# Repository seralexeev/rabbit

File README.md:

# Rabbit

A small home-built Ackermann rover that maps a flat on its own, drives to things you name ("drive to the fridge") and explains what it did. Everything is in this repo: the robot code, the web HUD, the telemetry store with its AI agent, the hardware design for the next version, and the build log.

Build log (Russian and English): **[rabbit0.dev](https://rabbit0.dev)** · Live HUD: https://live.rabbit0.dev (by personal link)

## What it does

- **Maps and localizes with one stereo camera.** A ZED 2i provides depth, visual-inertial odometry and object detection. nvblox builds a voxel map and a clearance grid on the GPU, and the robot relocalizes in its saved map after a restart. Relocalizing after being carried to another room is the open problem; RTAB-Map is replacing ZED GEN_3 for it.
- **Plans and drives like a car.** A Hybrid A* planner knows the robot's asymmetric turning radius and plans forward and reverse manoeuvres. A path tracker follows the plan on the rear axle, and a collision guard checks the swept footprint against the live obstacle scan.
- **Explores by itself.** It picks views by information gain and finishes a room before leaving it.
- **Takes orders in plain language.** The HUD chat, by text or voice, talks to Forge, an agent that answers from the recorded telemetry ("why did it stop at 03:12?") and can send trips after the operator approves them.
- **Records everything.** Every pose, command, decision with its reason, log line and power sample goes into Parquet files, queried with chDB (embedded ClickHouse).
- **Runs headless.** The HUD is only a viewer: the robot doesn't care whether anyone is watching.

| | |
|---|---|
|  |  |

## Hardware

| Part | What |
|---|---|
| Chassis | "Red Ackerman Racing Car" metal kit; front steering, rear drive. Wheelbase 0.17 m, 75 mm wheels, ~3.5 kg |
| Brain | NVIDIA Jetson Orin Nano Super 8 GB (JetPack 6, MAXN_SUPER, headless) |
| Camera | Stereolabs ZED 2i (depth, VIO, IMU, barometer, magnetometer) |
| Drive | 2 × Pololu 37D 70:1 12 V gearmotors on a RoboClaw 2x30A; electronic differential in software |
| Steering | AGFRC A50BHL brushless servo via a PCA9685 |
| Power | NEEWER PS099E V-mount battery (99 Wh, 4S Li-ion) and Pololu step-down regulators; INA4235 4-channel power monitor |
| Network | Wi-Fi only; NATS over websockets for the HUD; a Cloudflare tunnel for public access |

## Software

Python nodes talk over [NATS](https://nats.io) instead of ROS, one Docker container per node on the Jetson.

```
 ZED 2i ─► rabbit-zed ──pose/odom, obstacle scan, objects, map──► rabbit-nav ──drive──► rabbit-roboclaw ─► motors
              │                                              ▲        │                rabbit-steering ─► servo
              └─► rabbit-loc (RTAB-Map, map←odom)            │        └─ safety trips, recovery
                                   rabbit-planner (Hybrid A*) ┤
                                   rabbit-explore (frontiers) ┘
 rabbit-ina, rabbit-telemetry ─► power, Jetson, Docker, Wi-Fi
 all subjects ─► Forge (Parquet + chDB) ─► slabs, MCP, HUD chat agent
 HUD (React, three.js, uPlot) ◄── NATS websocket, served by rabbit-web (nginx)
```

| Path | What |
|---|---|
| [`workspaces/rabbit`](workspaces/rabbit) | robot nodes (`src/node/`), libraries (`src/lib/`), native extensions (nvblox, RTAB-Map), tests, the simulator |
| [`workspaces/web`](workspaces/web) | the HUD |
| [`workspaces/forge`](workspaces/forge) | Forge: telemetry writer, store, slabs, metric graph, MCP server and chat agent ([README](workspaces/forge/README.md)) |
| [`workspaces/blog`](workspaces/blog) | the build log at rabbit0.dev |
| [`workspaces/bench`](workspaces/bench) | localization benchmark and recording tools |
| [`workspaces/compose.yaml`](workspaces/compose.yaml), [`workspaces/nats`](workspaces/nats), [`workspaces/jetson`](workspaces/jetson) | services, NATS config, Jetson boot tuning |
| [`pcb/rabbit-body`](pcb/rabbit-body), [`cad/brackets`](cad/brackets), [`model`](model) | Rabbit 2.0 body PCB, 3D-printed mounts, chassis model |
| [`docs`](docs) | engineering log, reports, roadmap, open issues, lessons |
| [`scripts`](scripts) | deploy, bring-up, simulator, access links, blog |

## Rabbit 2.0

The next version splits the robot into a **brain** and a **body**:
- the Jetson keeps only GPU work: perception, localization and planning;
- a Raspberry Pi 4 becomes the body. It runs the motors, the steering, the power, an independent safety loop, a 360° lidar, ToF sensors and bumpers, a rear camera, Forge and the HUD.

The body electronics move from an acrylic deck full of modules onto one PCB shaped like the chassis deck. The board is generated from Python with KiCad and Freerouting.

| | |
|---|---|
|  |  |
|  |  |

Design: [architecture](docs/reports/2026-10-03-architecture-2.0.md) · [wiring](docs/reports/2026-10-03-architecture-2.0-wiring.md) · [BOM](docs/reports/2026-10-03-architecture-2.0-bom.md) · [body PCB](docs/reports/2026-10-03-body-pcb.md) · [mounts](docs/reports/2026-10-03-mounts.md) · [power](docs/reports/media/power-2.0.svg)

## Working on it

The project is developed mostly by coding agents. [`AGENTS.md`](AGENTS.md) holds the rules, and the skills in [`.claude/skills`](.claude/skills) hold the procedures:
- `rabbit-robot`: operating and deploying the robot;
- `rabbit-dev`: robot code and the HUD;
- `forge-dev`: Forge;
- `rabbit-blog`: the blog.

```sh
# robot tests
cd workspaces/rabbit && uv run --no-project --python 3.10 --with pytest --with numpy --with pydantic --with numba --with nats-py python -m pytest tests -q

# full-stack simulator on the Mac: local NATS + rabbit-sim + the real nav, planner and explore
scripts/sim.sh

# HUD dev server at https://localhost:3005
cd workspaces/web && node ../../.yarn/releases/yarn-4.9.3.cjs dev

# deploy named services to the robot
scripts/deploy.sh rabbit-nav rabbit-web

# after the robot was off: checks, deploy, tests, step by step
uv run scripts/bringup.py check
```

## Work log and blog

Every piece of significant work leaves two traces, written as part of the work:

1. **Engineering log** in [`docs/`](docs/README.md), in English and factual:
   - `docs/log/YYYY-MM-DD-<topic>.md`: what was tried and dropped, numbers, root causes;
   - [`docs/roadmap.md`](docs/roadmap.md): what's next;
   - [`docs/open-issues.md`](docs/open-issues.md): open questions and unresolved problems;
   - [`docs/lessons.md`](docs/lessons.md): rules learned the hard way.
2. **Blog post** at [rabbit0.dev](https://rabbit0.dev), in the author's voice:
   - source in [`workspaces/blog`](workspaces/blog): `README.ru.md` holds the Russian posts, `README.md` the English ones, `static/media/` the media;
   - `scripts/blog.sh build` renders the pages;
   - a push to `main` that touches `workspaces/blog` deploys it to GitHub Pages ([`.github/workflows/blog.yml`](.github/workflows/blog.yml)).

## Access links

The public HUD at https://live.rabbit0.dev opens only through a personal link; the LAN address (https://jetson.rabbit) stays open. Ask the agent "give me a link" (optionally "for Alice") or "remove Alice's link", or run it yourself:

```sh
scripts/links.sh              # list: name, date, link
scripts/links.sh add alice    # create a link, prints https://live.rabbit0.dev/k/<token>
scripts/links.sh rm alice     # revoke it: the open HUD is cut off within ~5 s
```

The registry lives only on the robot, in `/root/rabbit/workspaces/links/links.map`. Details are in the `rabbit-robot` skill.

Old hardware and setup scratch notes: [`docs/notes.md`](docs/notes.md).

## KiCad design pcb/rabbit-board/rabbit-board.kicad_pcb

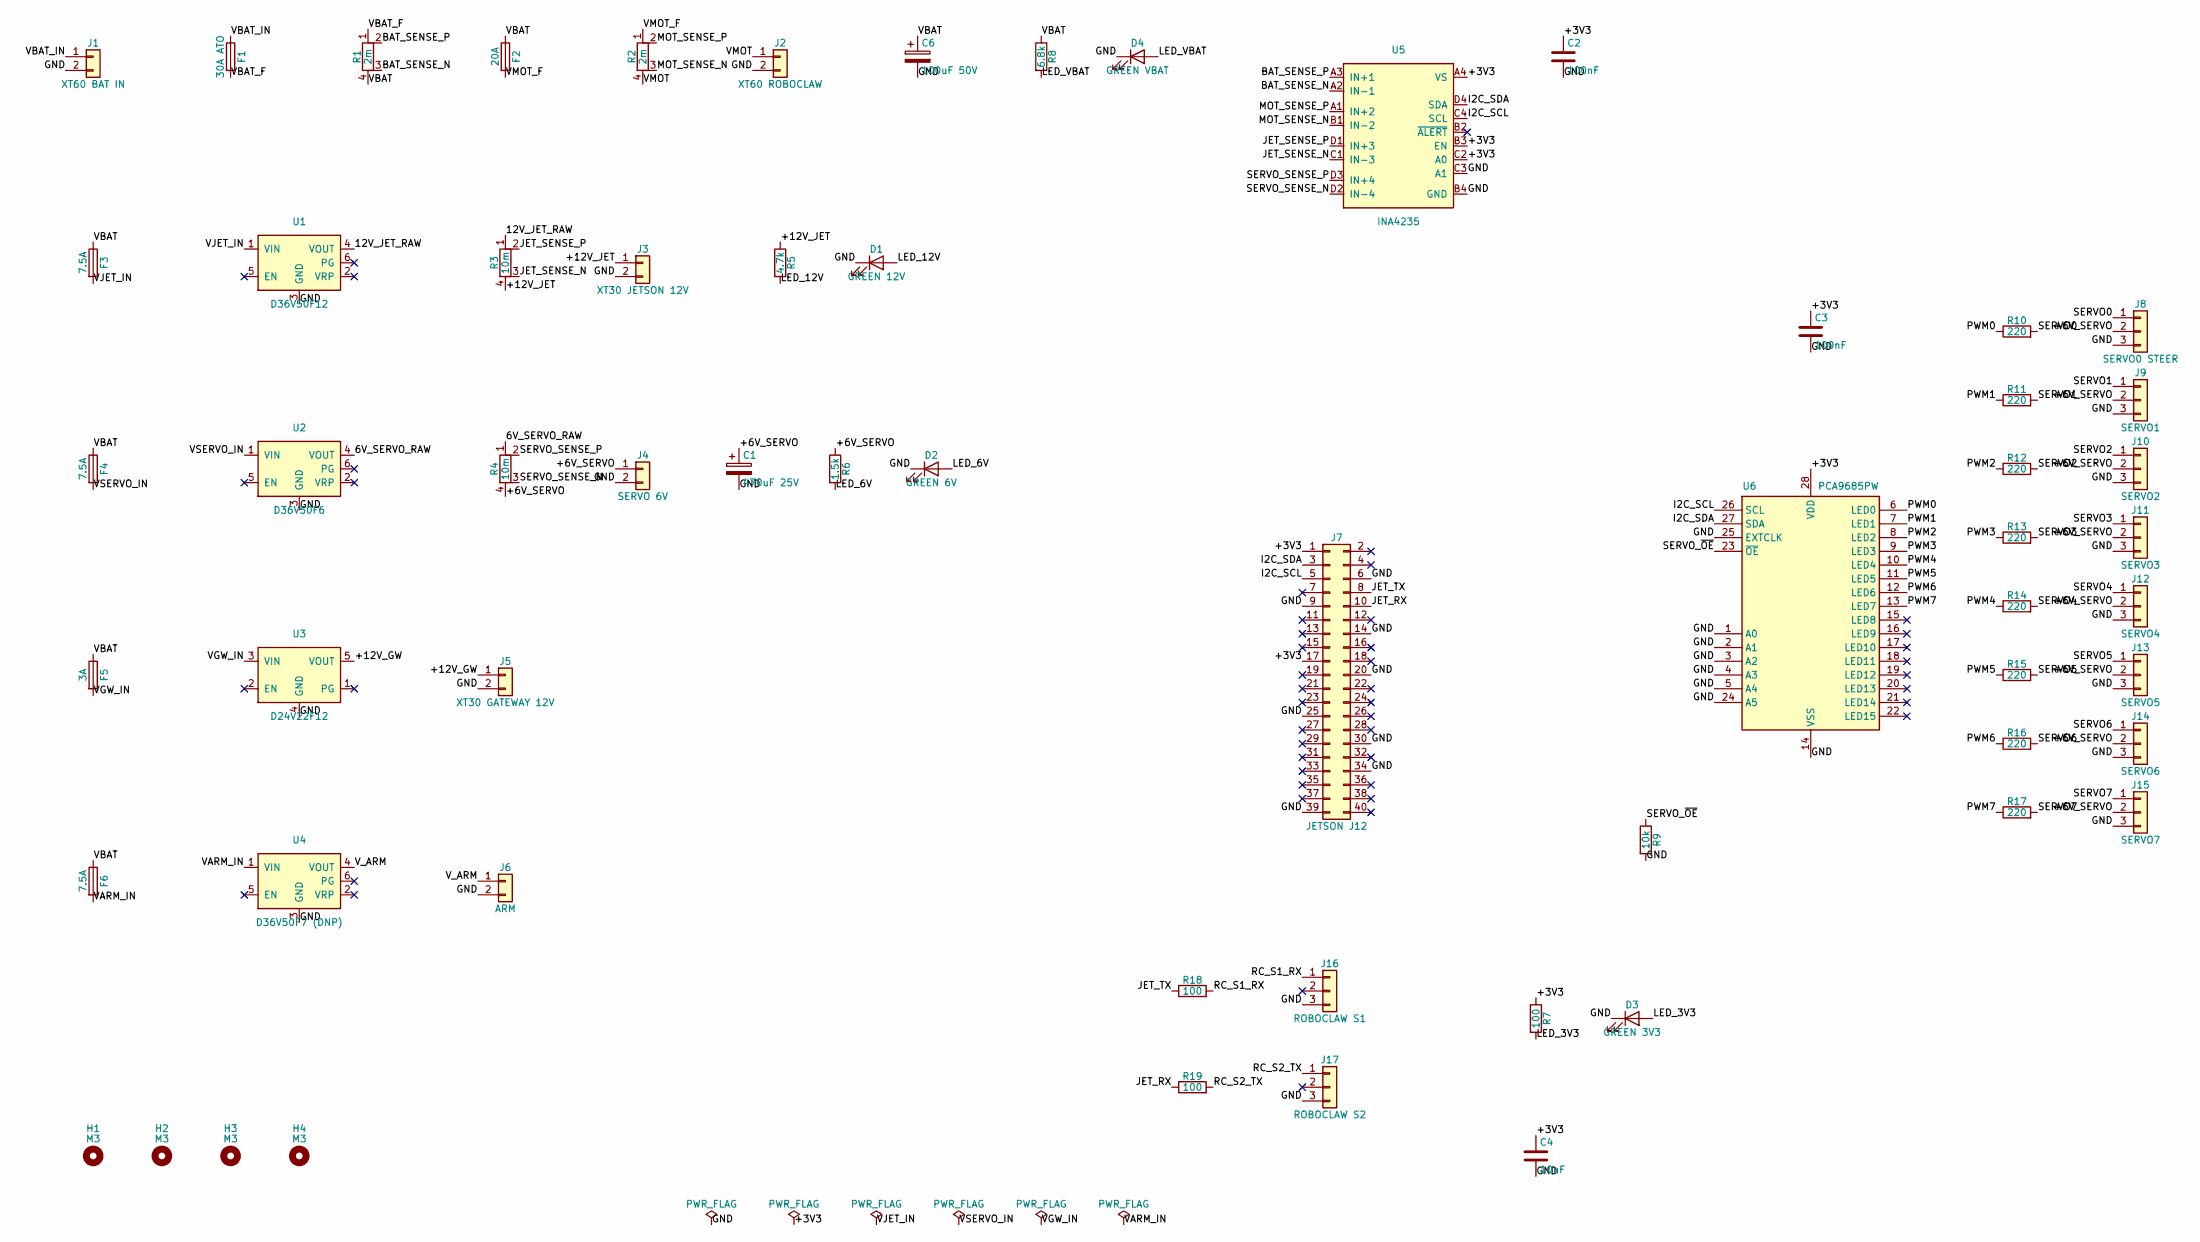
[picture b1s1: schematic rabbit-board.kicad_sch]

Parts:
C1: 470uF 25V; CP_Elec_8x10.5; LCSC C48935394
C2, C3: 100nF; C_0603_1608Metric; LCSC C14663
C4: 10uF; C_0805_2012Metric; LCSC C15850
C6: 100uF 50V; CP_Elec_6.3x7.7; LCSC C46550415
D1: GREEN 12V; LED_0805_2012Metric; LCSC C2297
D2: GREEN 6V; LED_0805_2012Metric; LCSC C2297
D3: GREEN 3V3; LED_0805_2012Metric; LCSC C2297
D4: GREEN VBAT; LED_0805_2012Metric; LCSC C2297
F1: 30A ATO; FuseHolder_Blade_ATO_Littelfuse_FLR_178.6165
F2: 20A; Fuseholder_Blade_Mini_Keystone_3568
F3, F4, F6: 7.5A; Fuseholder_Blade_Mini_Keystone_3568
F5: 3A; Fuseholder_Blade_Mini_Keystone_3568
H1, H2, H3, H4: M3; MountingHole_3.2mm_M3
J1: XT60 BAT IN; AMASS_XT60PW-M_1x02_P7.20mm_Horizontal
J2: XT60 ROBOCLAW; AMASS_XT60PW-F_1x02_P7.20mm_Horizontal
J3: XT30 JETSON 12V; AMASS_XT30PW-F_1x02_P2.50mm_Horizontal
J4: SERVO 6V; TerminalBlock_Phoenix_MKDS-1,5-2-5.08_1x02_P5.08mm_Horizont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
J5: XT30 GATEWAY 12V; AMASS_XT30PW-F_1x02_P2.50mm_Horizontal
J6: ARM; TerminalBlock_Phoenix_MKDS-1,5-2-5.08_1x02_P5.08mm_Horizont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
J7: JETSON J12; IDC-Header_2x20_P2.54mm_Vertical
J8: SERVO0 STEER; PinHeader_1x03_P2.54mm_Vertical
J9: SERVO1; PinHeader_1x03_P2.54mm_Vertical
J10: SERVO2; PinHeader_1x03_P2.54mm_Vertical
J11: SERVO3; PinHeader_1x03_P2.54mm_Vertical
J12: SERVO4; PinHeader_1x03_P2.54mm_Vertical
J13: SERVO5; PinHeader_1x03_P2.54mm_Vertical
J14: SERVO6; PinHeader_1x03_P2.54mm_Vertical
J15: SERVO7; PinHeader_1x03_P2.54mm_Vertical
J16: ROBOCLAW S1; PinHeader_1x03_P2.54mm_Vertical
J17: ROBOCLAW S2; PinHeader_1x03_P2.54mm_Vertical
R1, R2: 2m; R_Shunt_Vishay_WSK2512_6332Metric_T1.19mm; LCSC C3997408
R3, R4: 10m; R_Shunt_Vishay_WSK2512_6332Metric_T1.19mm; LCSC C3985410
R5: 4.7k; R_0603_1608Metric; LCSC C23162
R6: 1.5k; R_0603_1608Metric; LCSC C22843
R7, R18, R19: 100; R_0603_1608Metric; LCSC C22775
R8: 6.8k; R_0603_1608Metric; LCSC C23212
R9: 10k; R_0603_1608Metric; LCSC C25804
R10, R11, R12, R13, R14, R15, R16, R17: 220; R_0603_1608Metric; LCSC C22962
U1: D36V50F12; Pololu_D36V50Fx
U2: D36V50F6; Pololu_D36V50Fx
U3: D24V22F12; Pololu_D24V22Fx
U4: D36V50F7 (DNP); Pololu_D36V50Fx
U5: INA4235; TI_DSBGA-16_YBJ_1.5x1.5mm_P0.4mm; LCSC C33440856
U6: PCA9685PW; TSSOP-28_4.4x9.7mm_P0.65mm; LCSC C2678753

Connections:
/6V_SERVO_RAW: R4.1, U2.4 (VOUT)
/12V_JET_RAW: R3.1, U1.4 (VOUT)
/+3V3: C2.1, C3.1, C4.1, J7.1, J7.17, R7.1, U5.A4 (VS), U5.B3 (EN), U5.C2 (A0), U6.28 (VDD)
/+6V_SERVO: C1.1, J4.1, J8.2, J9.2, J10.2, J11.2, J12.2, J13.2, J14.2, J15.2, R4.4, R6.1
/+12V_GW: J5.1, U3.5 (VOUT)
/+12V_JET: J3.1, R3.4, R5.1
/BAT_SENSE_N: R1.3, U5.A2 (IN-1)
/BAT_SENSE_P: R1.2, U5.A3 (IN+1)
/GND: C1.2, C2.2, C3.2, C4.2, C6.2, D1.1 (K), D2.1 (K), D3.1 (K), D4.1 (K), J1.2, J2.2, J3.2, J4.2, J5.2, J6.2, J7.6, J7.9, J7.14, J7.20, J7.25, J7.30, J7.34, J7.39, J8.3, J9.3, J10.3, J11.3, J12.3, J13.3, J14.3, J15.3, J16.3, J17.3, R9.2, U1.3 (GND), U2.3 (GND), U3.4 (GND), U4.3 (GND), U5.B4 (GND), U5.C3 (A1), U6.1 (A0), U6.2 (A1), U6.3 (A2), U6.4 (A3), U6.5 (A4), U6.14 (VSS), U6.24 (A5), U6.25 (EXTCLK)
/I2C_SCL: J7.5, U5.C4 (SCL), U6.26 (SCL)
/I2C_SDA: J7.3, U5.D4 (SDA), U6.27 (SDA)
/JET_RX: J7.10, R19.1
/JET_SENSE_N: R3.3, U5.C1 (IN-3)
/JET_SENSE_P: R3.2, U5.D1 (IN+3)
/JET_TX: J7.8, R18.1
/LED_3V3: D3.2 (A), R7.2
/LED_6V: D2.2 (A), R6.2
/LED_12V: D1.2 (A), R5.2
/LED_VBAT: D4.2 (A), R8.2
/MOT_SENSE_N: R2.3, U5.B1 (IN-2)
/MOT_SENSE_P: R2.2, U5.A1 (IN+2)
/PWM0: R10.1, U6.6 (LED0)
/PWM1: R11.1, U6.7 (LED1)
/PWM2: R12.1, U6.8 (LED2)
/PWM3: R13.1, U6.9 (LED3)
/PWM4: R14.1, U6.10 (LED4)
/PWM5: R15.1, U6.11 (LED5)
/PWM6: R16.1, U6.12 (LED6)
/PWM7: R17.1, U6.13 (LED7)
/RC_S1_RX: J16.1, R18.2
/RC_S2_TX: J17.1, R19.2
/SERVO0: J8.1, R10.2
/SERVO1: J9.1, R11.2
/SERVO2: J10.1, R12.2
/SERVO3: J11.1, R13.2
/SERVO4: J12.1, R14.2
/SERVO5: J13.1, R15.2
/SERVO6: J14.1, R16.2
/SERVO7: J15.1, R17.2
/SERVO_SENSE_N: R4.3, U5.D2 (IN-4)
/SERVO_SENSE_P: R4.2, U5.D3 (IN+4)
/SERVO_~OE: R9.1, U6.23 (~OE)
/VARM_IN: F6.2, U4.1 (VIN)
/VBAT: C6.1, F2.1, F3.1, F4.1, F5.1, F6.1, R1.4, R8.1
/VBAT_F: F1.2, R1.1
/VBAT_IN: F1.1, J1.1
/VGW_IN: F5.2, U3.3 (VIN)
/VJET_IN: F3.2, U1.1 (VIN)
/VMOT: J2.1, R2.4
/VMOT_F: F2.2, R2.1
/VSERVO_IN: F4.2, U2.1 (VIN)
/V_ARM: J6.1, U4.4 (VOUT)

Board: 4 copper layers, 61 parts (0 on the bottom side), 52 nets, no tracks yet.

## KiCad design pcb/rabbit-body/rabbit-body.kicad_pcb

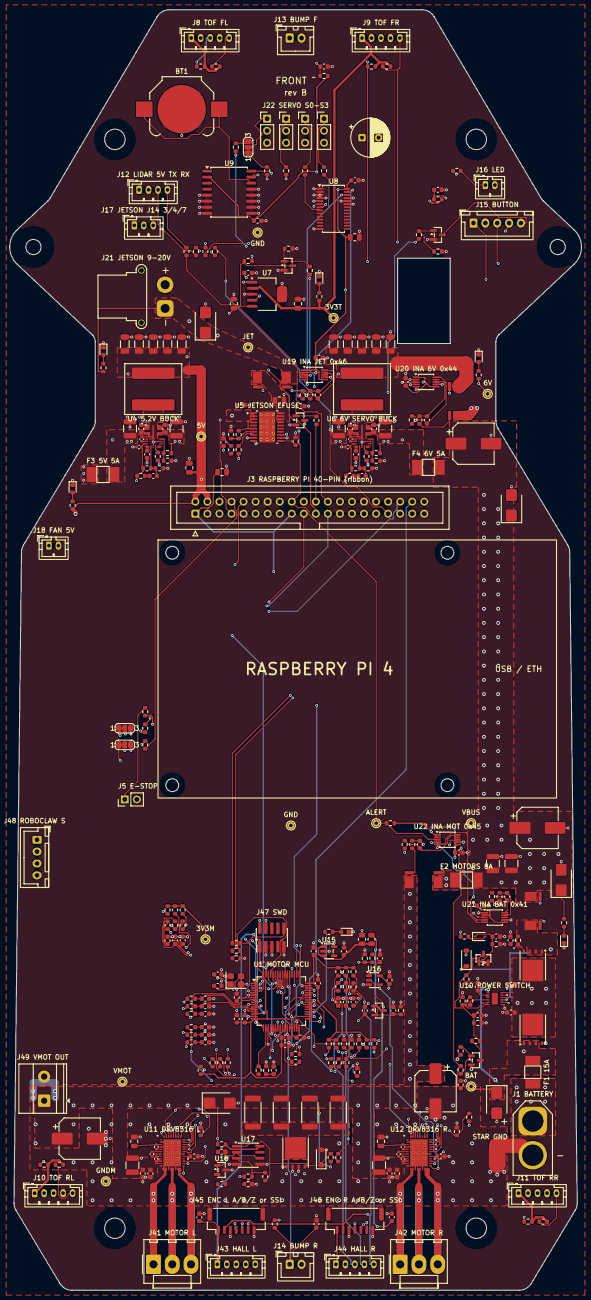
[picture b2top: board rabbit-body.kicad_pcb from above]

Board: 4 copper layers, 120.5 x 269.9 mm, 346 parts (0 on the bottom side), 226 nets.

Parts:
BT1: CR1220; BatteryHolder_Keystone_3000_1x12mm
C3, C5, C10, C11, C12, C14A, C14B, C19, C20, C21, C22, C26, C27, C28, C29, C63, C70, C71, C72, C73, C81, C83, C87, C120, C121, C122, C123, C1101, C1102, C1201, C1202: 100nF; C_0603_1608Metric
C4, C6, C7, C9, C13, C1106, C1206: 10uF; C_0805_2012Metric
C8, C24, C86: 10nF; C_0603_1608Metric
C14: 470uF 16V; CP_Radial_D8.0mm_P3.50mm
C18: 2.2uF; C_0603_1608Metric
C23, C80: 47nF; C_0603_1608Metric
C25, C55, C85, C90, C406, C451, C461, C606, C1107, C1207: 1uF; C_0603_1608Metric
C30, C33, C1109, C1209: 220uF 35V; CP_Elec_8x10.5
C31, C32, C401, C402, C601, C602, C1103, C1203: 10uF 50V; C_1210_3225Metric
C82: 1uF; C_0805_2012Metric
C84, C91: 4.7uF; C_0603_1608Metric
C88, C89: 18pF; C_0603_1608Metric
C100, C101, C102, C103, C104, C105, C1110, C1111, C1112, C1210, C1211, C1212: 1nF; C_0603_1608Metric
C403, C404, C603, C604: 470nF; C_0603_1608Metric
C405, C407, C605, C607: 100nF; C_0402_1005Metric
C408, C608: 10pF; C_0603_1608Metric
C410, C411, C412, C413, C414, C610, C611, C612, C613, C614: 22uF; C_1206_3216Metric
C1104, C1204: 1uF; C_0402_1005Metric
C1105, C1205: 47nF; C_0402_1005Metric
D1, D10, D13, D14: SMBJ20A; D_SMB
D2, D3, D4, D5, D6, D93: LED red; LED_0603_1608Metric
D7: SMBJ20CA; D_SMB
D8: BZT52C8V2; D_SOD-123
D9: 1N4148WS; D_SOD-323
D11: BZT52C12; D_SOD-123
D12: BAT54S; SOT-23
F1: 15A; Fuse_Littelfuse_NANO2_451_2410
F2: 8A; Fuse_Littelfuse_NANO2_451_2410
F3, F4: 5A; Fuse_Littelfuse_NANO2_451_2410
H1, H2, H3, H4: deck standoff M4; MountingHole_4.3mm_M4
H5, H6: deck standoff M3; MountingHole_3.2mm_M3
J1: XT60 BAT; AMASS_XT60-M_1x02_P7.20mm_Vertical
J3: Pi 40-pin; IDC-Header_2x20_P2.54mm_Vertical
J5: E-stop loop; PinHeader_1x02_P2.54mm_Vertical
J8, J9, J10, J11: ToF; JST_PH_B5B-PH-K_1x05_P2.00mm_Vertical
J12: lidar C1; JST_PH_B4B-PH-K_1x04_P2.00mm_Vertical
J13: bumpers front; JST_XH_B2B-XH-A_1x02_P2.50mm_Vertical
J14: bumpers rear; JST_XH_B2B-XH-A_1x02_P2.50mm_Vertical
J15: button; JST_XH_B5B-XH-A_1x05_P2.50mm_Vertical
J16: status LED; JST_PH_B2B-PH-K_1x02_P2.00mm_Vertical
J17: Jetson UART; JST_PH_B3B-PH-K_1x03_P2.00mm_Vertical
J18: Pi fan 5V; JST_PH_B2B-PH-K_1x02_P2.00mm_Vertical
J21: XT30 JETSON; AMASS_XT30PW-F_1x02_P2.50mm_Horizontal
J22: servo 0; PinHeader_1x03_P2.54mm_Vertical
J23: servo 1; PinHeader_1x03_P2.54mm_Vertical
J24: servo 2; PinHeader_1x03_P2.54mm_Vertical
J25: servo 3; PinHeader_1x03_P2.54mm_Vertical
J41, J42: motor phases; Molex_KK-396_A-41791-0003_1x03_P3.96mm_Vertical
J43, J44: Halls; JST_PH_B5B-PH-K_1x05_P2.00mm_Vertical
J45, J46: encoder; JST_GH_BM07B-GHS-TBT_1x07-1MP_P1.25mm_Vertical
J47: SWD; PinHeader_2x05_P1.27mm_Vertical_SMD
J48: RoboClaw S; JST_XH_B4B-XH-A_1x04_P2.50mm_Vertical
J49: MOT_BUS out; TerminalBlock_Phoenix_MKDS-1,5-2-5.08_1x02_P5.08mm_Horizont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
JP1: UART0 TX; SolderJumper-3_P1.3mm_Bridged12_RoundedPad1.0x1.5mm_NumberL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
JP2: UART0 RX; SolderJumper-3_P1.3mm_Bridged12_RoundedPad1.0x1.5mm_NumberL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
JP3: S0 source; SolderJumper-3_P1.3mm_Bridged12_RoundedPad1.0x1.5mm_NumberL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
L4, L6: 3.3uH; L_Coilcraft_XAL1010-XXX
MOD1: Raspberry Pi 4; RaspberryPi4_Standoffs
NT1: star GND; NetTie_3.5mm
Q1, Q2: BSC010N04LS; TDSON-8-1
Q3, Q5, Q7, Q8: AO3400A; SOT-23
Q4: MMBT3906; SOT-23
Q6: BSC026N04LS; TDSON-8-1
R1: 2mR 3W; R_Shunt_2512_Kelvin
R2, R4: 10mR 1W; R_Shunt_2512_Kelvin
R3: 5mR 3W; R_Shunt_2512_Kelvin
R9A, R17, R28, R31, R39, R41, R58, R60, R64, R65, R66, R81, R83, R90, R95, R99: 10k; R_0603_1608Metric
R10, R11, R12, R13, R16, R42, R55, R1102, R1103, R1104, R1202, R1203, R1204: 100; R_0603_1608Metric
R14, R15, R22, R24, R32B, R33B, R36, R48, R86, R91, R92, R93, R100, R101, R102, R103, R104, R105: 1k; R_0603_1608Metric
R14B, R18, R23, R25, R26, R43, R61, R63, R87, R96, R97, R98, R401, R404, R601, R604: 100k; R_0603_1608Metric
R27, R40A: 330; R_0603_1608Metric
R29, R30, R38, R56, R110, R111, R112, R113, R114, R115, R120A, R120B, R121A, R121B, R122A, R122B, R123A, R123B: 4.7k; R_0603_1608Metric
R32, R33, R34, R35, R89: 220; R_0603_1608Metric
R37: 1.5k; R_0603_1608Metric
R40, R82: 150k; R_0603_1608Metric
R44, R405, R605: 22k; R_0603_1608Metric
R45, R47: 47k; R_0603_1608Metric
R46: 220k; R_0603_1608Metric
R49: 1M; R_0603_1608Metric
R50, R51, R52, R53: 39R 2W; R_2512_6332Metric
R57: 60.4k; R_0603_1608Metric
R59: 1.5M; R_0603_1608Metric
R62: 33k; R_0603_1608Metric
R80: 68k; R_0603_1608Metric
R84: 3.9k; R_0603_1608Metric
R94: 5.1k; R_0603_1608Metric
R130, R131, R132, R133, R134, R135: 22; R_0603_1608Metric
R402: 24k; R_0603_1608Metric
R403, R603: 4.99k; R_0603_1608Metric
R406, R606: 39k; R_0603_1608Metric
R451, R461: 10; R_0805_2012Metric
R602: 20k; R_0603_1608Metric
R701, R702, R711, R712, R721, R722, R731, R732: 10; R_0603_1608Metric
R1101, R1201: 22; R_0402_1005Metric
RT65, RT66: NTC 10k; R_0603_1608Metric
TP1: VBUS; TestPoint_THTPad_D1.5mm_Drill0.7mm
TP2: +5V; TestPoint_THTPad_D1.5mm_Drill0.7mm
TP3: SERVO_6V; TestPoint_THTPad_D1.5mm_Drill0.7mm
TP4: JET_PWR; TestPoint_THTPad_D1.5mm_Drill0.7mm
TP5: +3V3_TOF; TestPoint_THTPad_D1.5mm_Drill0.7mm
TP6, TP7: GND; TestPoint_THTPad_D1.5mm_Drill0.7mm
TP8: INA_ALERT; TestPoint_THTPad_D1.5mm_Drill0.7mm
TP9: MOT_BUS; TestPoint_THTPad_D1.5mm_Drill0.7mm
TP10: +3V3_MCU; TestPoint_THTPad_D1.5mm_Drill0.7mm
TP11: GND_MOT; TestPoint_THTPad_D1.5mm_Drill0.7mm
TP12: BAT_F; TestPoint_THTPad_D1.5mm_Drill0.7mm
U1: STM32G474RET6; LQFP-64_10x10mm_P0.5mm
U4, U6: LM61495; TI_RPH0016B_VQFN-HR-16_3.5x4.5mm
U5: TPS16630; HTSSOP-20-1EP_4.4x6.5mm_P0.65mm_EP3.4x6.5mm_Mask2.96x2.96mm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
U7: TPS73733; SOT-223-6
U8: PCA9685PW; TSSOP-28_4.4x9.7mm_P0.65mm
U9: DS3231SN; SOIC-16W_7.5x10.3mm_P1.27mm
U10: LM74800; TI_DRR0012E_WSON-12_3x3mm_P0.5mm_EP1.3x2.5mm
U11, U12: DRV8316CR; TI_RGF0040E_VQFN-40_5x7mm_P0.5mm_EP3.7x5.7mm
U15: TLV75533; SOT-23-5
U16: SN74LVC1G132; SOT-23-5
U17: LM393; SOIC-8_3.9x4.9mm_P1.27mm
U18: TL431; SOT-23
U19, U20, U21, U22: INA226; MSOP-10_3x3mm_P0.5mm
Y1: 8MHz; Crystal_SMD_3225-4Pin_3.2x2.5mm

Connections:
5V_HALL_L: C451.1, J43.1, J45.1, R451.2
5V_HALL_R: C461.1, J44.1, J46.1, R461.2
6V_RAW: C607.2, C610.1, C611.1, C612.1, C613.1, C614.1, L6.2, R2.1, R601.1, R603.1, U6.5
+3V3_MCU: C19.1, C84.1, C85.1, C86.1, C91.1, C120.1, C121.1, C122.1, C123.1, J45.2, J46.2, J47.1, R9A.2, R65.1, R66.1, R94.2, R95.2, R99.2, R110.2, R111.2, R112.2, R113.2, R114.2, R115.2, TP10.1, U1.1, U1.16, U1.28, U1.29, U1.32, U1.48, U1.64, U15.5, U16.5
+3V3_PI: C3.1, C4.1, C5.1, C13.1, C27.1, C28.1, C29.1, C83.1, J3.1, J3.17, R28.2, R29.2, R30.2, R31.2, U8.28, U9.2, U19.1, U19.6, U20.1, U20.6, U21.2, U21.6, U22.1, U22.2, U22.6
+3V3_TOF: C7.1, J8.1, J9.1, J10.1, J11.1, R40A.1, R120A.2, R120B.2, R121A.2, R121B.2, R122A.2, R122B.2, R123A.2, R123B.2, TP5.1, U7.2
+5V: C6.1, C9.1, C90.1, C407.2, C410.1, C411.1, C412.1, C413.1, C414.1, J3.2, J3.4, J12.1, J15.4, J18.1, L4.2, R26.2, R36.1, R401.1, R403.1, R451.1, R461.1, TP2.1, U4.5, U7.1, U15.1, U15.3
ADC_AL: C1110.1, R1102.2, U1.12
ADC_AR: C1210.1, R1202.2, U1.9
ADC_BL: C1111.1, R1103.2, U1.13
ADC_BR: C1211.1, R1203.2, U1.10
ADC_CL: C1112.1, R1104.2, U1.8
ADC_CR: C1212.1, R1204.2, U1.11
ALIVE_AC: C14A.2, D12.3
ALIVE_DET: C14B.1, D12.2, R14B.1, U16.2
AVDD_L: C1107.1, U11.25, U11.37
AVDD_R: C1207.1, U12.25, U12.37
BAT_F: C22.1, D7.1, F1.2, Q1.1, Q1.2, Q1.3, Q4.2, R43.1, TP12.1, U10.2, U10.3
BAT_IN: F1.1, J1.1
BK_L: C1106.1, R1101.2, U11.3
BK_R: C1206.1, R1201.2, U12.3
BODY_IN: C401.1, C402.1, C403.1, C404.1, F3.2, R404.2, U4.2, U4.14
BOOT4: C405.1, U4.3, U4.4
BOOT6: C605.1, U6.3, U6.4
BRK_D: Q6.5, R50.1, R51.1, R52.1, R53.1
BRK_G: D11.1, Q6.4, R59.1, R60.2, R61.1, U17.1
BRK_REF: R56.2, U17.2, U17.6, U18.1, U18.2
BRK_SENSE: R61.2, R62.1, U1.23
BRK_SNS: R57.2, R58.1, R59.2, U17.3
BRK_VCC: C55.1, R55.2, U17.8
BTN_LED_K: J15.5, Q3.3
BTN_ON: C26.1, J15.1, R44.2
BUMPER_FRONT: C11.1, J3.38, J13.1, R29.1, R32B.1
BUMPER_REAR: C12.1, J3.40, J14.1, R30.1, R33B.1
BUMP_F_M: R32B.2, U1.25
BUMP_R_M: R33B.2, U1.26
CPH_L: C1105.1, U11.7
CPH_R: C1205.1, U12.7
CPL_L: C1105.2, U11.6
CPL_R: C1205.2, U12.6
CP_L: C1104.2, U11.8
CP_R: C1204.2, U12.8
DG: Q1.4, U10.1
DRVOFF: U11.21, U12.21, U16.4
DRV_NFAULT: R94.1, U1.20, U11.22, U12.22
DRV_NSLEEP: R96.1, U1.24, U11.23, U12.23
EN4: R404.1, R405.1, U4.13
EN6: R604.1, R605.1, U6.13
ENC_L_A: J45.4, R131.2
ENC_L_A_M: R131.1, U1.59
ENC_L_B: J45.5, R132.1
ENC_L_B_M: R132.2, U1.60
ENC_L_Z: J45.6, R130.2
ENC_L_Z_M: R130.1, U1.56
ENC_R_A: J46.4, R134.2
ENC_R_A_M: R134.1, U1.57
ENC_R_B: J46.5, R135.1
ENC_R_B_M: R135.2, U1.58
ENC_R_Z: J46.6, R133.2
ENC_R_Z_M: R133.1, U1.41
ESTOP: J5.2, J48.3, R17.1, R18.1, U1.34, U1.55
ESTOP_A: J5.1, R16.2
ESTOP_DLY: C18.1, R18.2, U16.1
FB4: C408.2, R401.2, R402.1, U4.7
FB6: C608.2, R601.2, R602.1, U6.7
FF4: C408.1, R403.2
FF6: C608.1, R603.2
GND: BT1.2, C3.2, C4.2, C5.2, C6.2, C7.2, C8.2, C9.2, C10.2, C11.2, C12.2, C13.2, C14.2, C14B.2, C18.2, C19.2, C21.2, C22.2, C23.2, C24.2, C25.2, C26.2, C27.2, C28.2, C29.2, C30.2, C31.2, C32.2, C33.2, C63.2, C80.2, C81.2, C82.2, C83.2, C84.2, C85.2, C86.2, C87.2, C88.2, C89.2, C90.2, C91.2, C100.2, C101.2, C102.2, C103.2, C104.2, C105.2, C120.2, C121.2, C122.2, C123.2, C401.2, C402.2, C403.2, C404.2, C406.1, C407.1, C410.2, C411.2, C412.2, C413.2, C414.2, C451.2, C461.2, C601.2, C602.2, C603.2, C604.2, C606.1, C607.1, C610.2, C611.2, C612.2, C613.2, C614.2, C1110.2, C1111.2, C1112.2, C1210.2, C1211.2, C1212.2, D1.2, D2.1, D3.1, D4.1, D5.1, D6.1, D7.2, D12.1, D13.2, D14.2, D93.1, J1.2, J3.6, J3.9, J3.14, J3.20, J3.25, J3.30, J3.34, J3.39, J8.2, J8.4, J9.2, J9.4, J10.2, J10.4, J11.2, J11.4, J12.2, J13.2, J14.2, J15.2, J16.2, J17.3, J18.2, J21.2, J22.3, J23.3, J24.3, J25.3, J43.2, J44.2, J45.3, J45.7, J46.3, J46.7, J47.3, J47.5, J47.9, J48.4, NT1.2, Q3.2, Q5.2, Q7.2, Q8.2, R14B.2, R17.2, R23.2, R25.2, R41.2, R46.2, R49.2, R62.2, R64.2, R81.2, R83.2, R84.2, R87.2, R90.2, R96.2, R97.2, R98.2, R402.2, R405.2, R406.1, R602.2, R605.2, R606.1, TP6.1, TP7.1, U1.15, U1.27, U1.31, U1.47, U1.63, U4.1, U4.8, U4.11, U4.12, U4.15, U5.9, U5.12, U5.21, U6.1, U6.8, U6.11, U6.12, U6.15, U7.3, U7.6, U8.1, U8.2, U8.3, U8.4, U8.5, U8.14, U8.23, U8.24, U8.25, U9.5, U9.6, U9.7, U9.8, U9.9, U9.10, U9.11, U9.12, U9.13, U10.7, U15.2, U16.3, U19.7, U20.2, U20.7, U21.1, U21.7, U22.7, Y1.2, Y1.4
GND_MOT: C55.2, C1101.1, C1102.1, C1103.2, C1106.2, C1107.2, C1109.2, C1201.1, C1202.1, C1203.2, C1206.2, C1207.2, C1209.2, D10.2, D11.2, J49.2, NT1.1, Q6.1, Q6.2, Q6.3, R58.2, RT65.2, RT66.2, TP11.1, U11.2, U11.4, U11.12, U11.15, U11.18, U11.26, U11.41, U12.2, U12.4, U12.12, U12.15, U12.18, U12.26, U12.41, U17.4, U17.5, U18.3
GPIO0: J3.27, R91.1
GPIO1: J3.28, R92.1
GPIO8: J3.24, R12.1
GPIO9: J3.21, R13.2
GPIO12: J3.32, R14.1
GPIO13: J3.33, R15.2
GPIO14: J3.8, R10.1
GPIO15: J3.10, R11.2
GPIO16: J3.36, R16.1
GPIO17: J3.11, R48.1
GPIO18: J3.12, R22.1
GPIO19: J3.35, R27.1
GPIO25: J3.22, R86.1
GPIO27: J3.13, R24.1
HG: Q2.4, R42.1, U10.8
HG_DV: C23.1, R42.2
HLA: J43.3, R100.1, R110.1
HLA_M: C100.1, R100.2, U1.2
HLB: J43.4, R101.1, R111.1
HLB_M: C101.1, R101.2, U1.3
HLC: J43.5, R102.1, R112.1
HLC_M: C102.1, R102.2, U1.4
HOLD_Z: D8.2, R47.1
HRA: J44.3, R103.1, R113.1
HRA_M: C103.1, R103.2, U1.45
HRB: J44.4, R104.1, R114.1
HRB_M: C104.1, R104.2, U1.46
HRC: J44.5, R105.1, R115.1
HRC_M: C105.1, R105.2, U1.62
I2C1_SCL: J3.5, U8.26, U9.16, U19.5, U20.5, U21.5, U22.5
I2C1_SDA: J3.3, U8.27, U9.15, U19.2, U19.4, U20.4, U21.4, U22.4
INA1_N: C70.2, R702.2, U21.8, U21.9
INA1_P: C70.1, R701.2, U21.10
INA2_N: C73.2, R732.2, U20.8, U20.9
INA2_P: C73.1, R731.2, U20.10
INA3_N: C71.2, R712.2, U22.8, U22.9
INA3_P: C71.1, R711.2, U22.10
INA4_N: C72.2, R722.2, U19.8, U19.9
INA4_P: C72.1, R721.2, U19.10
INA_ALERT: J3.18, R31.1, TP8.1, U19.3, U20.3, U21.3, U22.3
INHA_L: U1.42, U11.27
INHA_R: U1.38, U12.27
INHB_L: U1.43, U11.29
INHB_R: U1.39, U12.29
INHC_L: U1.44, U11.31
INHC_R: U1.40, U12.31
INL_L: R97.1, U1.30, U11.28, U11.30, U11.32
INL_R: R98.1, U1.19, U12.28, U12.30, U12.32
JET_DVDT: C80.1, U5.10
JET_ILIM: R84.1, U5.11
JET_OUT: C82.1, R4.1, U5.18, U5.19, U5.20
JET_OVP: R82.2, R83.1, U5.8
JET_PWR: D14.1, J21.1, R4.2, R38.1, TP4.1
JET_SHDN: Q7.3, U5.13
JET_UART_RX: J17.1, R14.2
JET_UART_TX: J17.2, R15.1
JET_UVLO: R80.1, R81.1, U5.7
LATCH_B: Q4.1, R43.2, R44.1
LATCH_C: Q4.3, R45.1
LED5_A: D2.2, R36.2
LED6_A: D3.2, R37.2
LED12_A: D4.2, R38.2
LED33_A: D6.2, R40A.2
LEDB_A: D5.2, R39.1
LIDAR_RX: J12.4, R12.2
LIDAR_TX: J12.3, R13.1
LM_CAP: C20.1, U10.11
LM_EN: C24.1, Q5.3, R45.2, R46.1, R47.2, U10.6
LM_OV: R40.2, R41.1, U10.5
LM_SW: R40.1, U10.4
MCU_ALIVE: C14A.1, U1.35
MCU_BOOT0: R90.1, R91.2, U1.61
MCU_LED: R93.1, U1.36
MCU_LED_A: D93.2, R93.2
MCU_NRST: C87.1, J47.10, R92.2, U1.7
MCU_RX: JP1.1, U1.17
MCU_TX: JP2.1, U1.14
MLA: J41.1, U11.13, U11.14
MLB: J41.2, U11.16, U11.17
MLC: J41.3, U11.19, U11.20
MOT_BUS: C1101.2, C1102.2, C1103.1, C1104.1, C1109.1, C1201.2, C1202.2, C1203.1, C1204.1, C1209.1, D10.1, J49.1, R3.2, R50.2, R51.2, R52.2, R53.2, R55.1, R56.1, R57.1, R60.1, R63.1, TP9.1, U11.9, U11.10, U11.11, U12.9, U12.10, U12.11
MOT_F: F2.2, R3.1
MRA: J42.1, U12.13, U12.14
MRB: J42.2, U12.16, U12.17
MRC: J42.3, U12.19, U12.20
NSCS_L: R99.1, U1.51, U11.36
NSCS_R: R9A.1, U1.37, U12.36
NTC_L: R65.2, RT65.1, U1.22
NTC_R: R66.2, RT66.1, U1.33
OFF_A: D9.2, R48.2
OFF_G: C25.1, D9.1, Q5.1, R49.1
OSC_IN: C88.1, U1.5, Y1.1
OSC_OUT: C89.1, U1.6, Y1.3
PCA_LED0: R32.1, U8.6
PCA_LED1: R33.1, U8.7
PCA_LED2: R34.1, U8.8
PCA_LED3: R35.1, U8.9
POWER_BTN: C10.1, J3.37, J15.3, R28.1
PWM0: J22.1, JP3.2
PWM0_MCU: JP3.3, R89.2
PWM0_PCA: JP3.1, R32.2
PWM1: J23.1, R33.2
PWM2: J24.1, R34.2
PWM3: J25.1, R35.2
Q3_G: Q3.1, R24.2, R25.1
Q7_G: Q7.1, R86.2, R87.1
Q8_G: Q8.1, R22.2, R23.1
RC_S1: J48.1, JP1.3
RC_S2: J48.2, JP2.3
RT4: R406.2, U4.9
RT6: R606.2, U6.9
RTC_VBAT: BT1.1, U9.14
SERVO_6V: C14.1, J22.2, J23.2, J24.2, J25.2, R2.2, R37.1, TP3.1
SERVO_MCU: R89.1, U1.21
SH1_N: R1.4, R702.1
SH1_P: R1.3, R701.1
SH2_N: R2.4, R732.1
SH2_P: R2.3, R731.1
SH3_N: R3.4, R712.1
SH3_P: R3.3, R711.1
SH4_N: R4.4, R722.1
SH4_P: R4.3, R721.1
SOA_L: R1102.1, U11.40
SOA_R: R1202.1, U12.40
SOB_L: R1103.1, U11.39
SOB_R: R1203.1, U12.39
SOC_L: R1104.1, U11.38
SOC_R: R1204.1, U12.38
SPI_MISO: R95.1, U1.53, U11.33, U12.33
SPI_MOSI: U1.54, U11.34, U12.34
SPI_SCK: U1.52, U11.35, U12.35
STATUS_LED_A: J16.1, R27.2
STEER_IN: C601.1, C602.1, C603.1, C604.1, F4.2, R604.2, U6.2, U6.14
SW4: C405.2, L4.1, U4.16
SW6: C605.2, L6.1, U6.16
SWBK_L: R1101.1, U11.5
SWBK_R: R1201.1, U12.5
SWCLK: J47.4, U1.50
SWDIO: J47.2, U1.49
SW_MID: C20.2, C21.1, Q1.5, Q2.5, U10.10, U10.12
TOF_EN: Q8.3, R26.1, U7.5
TOF_FL_SCL: J3.29, J8.3, R120A.1
TOF_FL_SDA: J3.7, J8.5, R120B.1
TOF_FR_SCL: J3.26, J9.3, R121A.1
TOF_FR_SDA: J3.31, J9.5, R121B.1
TOF_RL_SCL: J3.23, J10.3, R122A.1
TOF_RL_SDA: J3.19, J10.5, R122B.1
TOF_RR_SCL: J3.16, J11.3, R123A.1
TOF_RR_SDA: J3.15, J11.5, R123B.1
TPS_NR: C8.1, U7.4
UART0_RX: JP2.2, R11.1
UART0_TX: JP1.2, R10.2
VBUS: C30.1, C31.1, C32.1, C33.1, C81.1, D1.1, D13.1, F2.1, F3.1, F4.1, R1.2, R39.2, R80.2, R82.1, TP1.1, U5.1, U5.2, U5.3, U5.6
VBUS_RAW: D8.1, Q2.1, Q2.2, Q2.3, R1.1, U10.9
VCC4: C406.2, U4.6
VCC6: C606.2, U6.6
VMOT_SENSE: C63.1, R63.2, R64.1, U1.18

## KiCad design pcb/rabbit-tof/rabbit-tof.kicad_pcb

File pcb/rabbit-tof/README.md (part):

# ToF carrier (VL53L8CX), rev A

This is a 22 × 18 mm carrier for the ST VL53L8CX 8×8 multizone ToF sensor. It plugs into one ToF port of the body board (`pcb/rabbit-body-c`) with a 100 mm JST GH-6 cable, pin 1 to pin 1. Planned quantity: 10 boards, 6 used and 4 spares.

`gen/design.py` is the single source of truth for parts, nets and positions. Everything else is generated from it:

```
gen/make.sh                      # STEP model of the sensor, footprints, placement + pours, Freerouting, cleanup, fill, DRC
PY=/Applications/KiCad/KiCad.app/Contents/Frameworks/Python.framework/Versions/3.9/bin/python3
$PY gen/check_netlist.py --board # netlist and placement checks, board == design.py
python3 gen/stock.py 10          # JLC stock for 10 boards -> fab/stock.json, fab/rabbit-tof-revA-stock.csv
$PY gen/fab.py                   # Gerbers zip, JLC BOM + CPL, full BOM, board STEP
gen/render.sh                    # renders/front.png, back.png, iso_front.png, iso_back.png
```

Board frame: mm, origin at the board centre, X right, Y up, looking at the sensor (front) face. In KiCad the page position is x = 100 + X, y = 100 − Y.

## Sources

| Document | Where | Cited as |
|---|---|---|
| VL53L8CX datasheet DS14161 **Rev 12** (July 2025), from st.com | `data/datasheets/st/vl53l8cx-DS14161-rev12.pdf` (Rev 7 from LCSC alongside) | DS p.N |
| AN5897 Rev 2 "PCB thermal guidelines for the VL53L8 ToF sensor family" | read on st.com; the browser could not save the file | AN5897 p.N |
| TI LP5907 SNVS798Q | `data/datasheets/ti/lp5907.pdf` | LP5907 p.N |
| TI LSF0204 SLVSCP5H | `data/datasheets/ti/lsf0204.pdf` | LSF p.N |
| TI TPS25947 SLVSFC9C (the body board's port eFuse TPS259470L) | `data/datasheets/ti/tps25947.pdf` | TPS25947 p.N |
| JST GH catalogue | `data/datasheets/jst/GH-catalog.pdf` | — |

## Design decisions

### 1. Supplies: 3.3 V alone is not possible, so the board has a 1.8 V LDO

The brief asked for a single 3.3 V supply "if the datasheet allows". It does not:
- CORE_1V8 is a 1.8 V supply. IOVDD is 1.2 V or 1.8 V, and both have an **absolute maximum of 1.98 V** (DS p.20 table 11, p.4 table 1).
- Rev 12 has no internal-LDO or 3.3 V IOVDD option.
- The Rev 7 copy from LCSC says the same.

The supplies are therefore:
- **AVDD** comes from port pin 2 (the body board's switched, eFuse-limited 3.3 V).
- **CORE_1V8 and IOVDD** share one TI **LP5907MFX-1.8** (C92498). DS p.20 recommends one supply for both when IOVDD is 1.8 V.
- **Current:** CORE draws 50 mA typical and 80 mA max while ranging, plus 10 mA peaks (DS p.21 table 14). That gives 135 mW in the LDO at most.
- **Power-up slew (DS p.11 table 5):** after AVDD is stable, CORE_1V8 and IOVDD must rise at ≥ 0.012 V/µs. In the "start together" case AVDD also needs ≥ 0.001 V/µs.
- **The port ramp is too slow for "start together":** the body board's TPS259470L with CdVdt 2.2 nF ramps at 2000 / 2200 pF = 0.9 V/ms (TPS25947 eq. 4). With the IdVdt spread, the slowest case is 0.33 V/ms.
  - An LDO enabled with AVDD would therefore track AVDD in dropout at 0.0003–0.0009 V/µs, which violates the table.
- **Enable delay:** EN is delayed by **R1 100k / C6 1 µF**. The LP5907's internal 1 MΩ EN pull-down is included in the calculation.
  - `check_netlist.py` simulates the slowest port ramp, including a generous 10 µA hot reverse leakage of D1 that charges EN: AVDD reaches 3.13 V at 9.4 ms, and EN reaches VIH max (1.2 V) at 40 ms.
  - With the fastest EN threshold (VIL 0.4 V), EN still crosses after AVDD is up. This is the DS's "AVDD stable followed by CORE_1V8 and IOVDD" row. D1 is reverse-biased while the rail rises (EN < rail), so it does not change the sequence.
- **LDO start-up:** the LP5907 then starts in t_ON 80 µs typical / 150 µs max to 95 % (LP5907 p.6). That is about 0.021 V/µs typical.
  - If all of the 150 µs max were ramp, the average would be 0.011 V/µs. Most of t_ON is the internal delay, so this is listed as a bench check (V13).
- **Why not TPS7A20 or TLV755:** TPS7A2018 (750 µs) and TLV75518 (550 µs) start too slowly for the 0.012 V/µs rule.
- **Power-down and re-enable (review round 2, T-4):** the port eFuse has no output discharge, so without help the rail and C6 would decay only through leakage and the 1 MΩ (τ ≈ 1 s).
  - A quick re-enable would then find EN still high. The LDO would track AVDD up in dropout, which is too slow for DS p.11 table 5.
  - **R9** (10k, +3V3 to GND, 1.1 mW while on) bleeds the rail. The rail is about 12 µF (C1 + C4 here, plus the body board's 1 µF eFuse output cap), so τ = 0.12 s.
  - **D1** (Diodes BAT54WS-7-F, C124205; anode EN, cathode +3V3) pulls EN down with the rail.
  - `check_netlist.py` simulates the decay with a 0.15 V Schottky drop: EN falls below 0.35 V (VIL is 0.4 V) 350 ms after the port turns off. The LP5907 then discharges +1V8 through its 230 Ω (LP5907 p.3).
  - **A sensor reset by power-cycling the port must keep the port off for ≥ 0.8 s** (twice the computed time). V13 measures it.
- **Decoupling (DS p.8 fig. 5):**
  - **AVDD:** C1 is a 10 µF 0603 X5R. The DS asks for 4.7 µF; 10 µF keeps ≥ 4.7 µF effective at 3.3 V bias. It sits 1.8 mm from pin C4.
  - **CORE_1V8:** C2 100 nF, 1.4 mm from B7.
  - **IOVDD:** C3 100 nF, 1.3 mm from A3. It is tucked under the A row, and a `.kicad_dru` rule allows its courtyard overlap.
  - **LDO:** 1 µF on its input and on its output (LP5907 p.4).

### 2. Interface: I2C through a TI LSF0204

**Strapping (DS p.7 table 3, p.8 fig. 5, I2C mode):**
- SPI_I2C_N (C1) and NCS (C2) each have a 47k pull-down (R7, R8).
- MISO (C5) is not connected.
- RSVD1–3 (A6, A7, C6) and both GND pins go to GND.

**Pull-ups on the sensor side, all to 1.8 V (DS p.7):**
- SDA and SCL: 2.2k each (R2, R3).
- GPIO1 = INT: 47k (R4).
- LPn: 47k (R5).
- GPIO2 = SYNC: 47k (R6). SYNC is not used; DS Rev 11+ renamed A1/B1 to GPIO1/GPIO2.

**Level translation:** all digital pins must be driven at the IOVDD level (DS p.7 note), and the body board works at 3.3 V. A TI **LSF0204PWR** (C202288) translates SDA, SCL, INT and LPn (LSF p.13 fig. 10-1):
- Vref_A = 1.8 V and Vref_B = 3.3 V.
- EN is tied to Vref_A, so the switches stay off and isolate the 3.3 V side until the 1.8 V rail is up. The sensor is never back-powered through SDA/SCL.
- Because it is a pass-FET translator, both open-drain lines (SDA, SCL, INT) and the push-pull LPn drive from the body board's TCA6416A (through its 1k) pass through without direction control.

**No duplicate parts on the 3.3 V side.** The body board already has the 4.7k SDA/SCL and 10k INT pull-ups to the port's switched 3.3 V, the 1k in LPn and the ESD diodes.

**LPn has a pull-up, not a pull-down.** DS p.7 says LPn low disables I2C, and asks for a 47k pull-up to IOVDD when the pin is not driven.
- Each sensor has its own TCA9548A channel, so the shared 0x29 address never collides and the sensor should talk as soon as it is powered.
- While the TCA6416A pin is still an input after reset, R5 holds LPn high.
- The Pi can still drive LPn low through the translator to drop a sensor off the bus.
- A 47k pull-down would instead leave I2C off until the Pi drives LPn.

### 3. Land pattern (`gen/footprints.py`, `lib/rabbit_tof.pretty/ST_VL53L8CX_LGA-16_6.4x3.0mm`)

**Pads (DS p.37 fig. 33, "view through top of module"):**
- 14 pads, 0.500 × 0.515, at 0.750 pitch.
- The rows are 1.315 from the centre line to the outer pad edge, with a 0.200 gap to the thermal pad.
- Thermal pad B4: 2.316 × 1.200.
- B1/B7: 0.535 × 0.500, centred at ±2.6675.
- **A1 has ST's pin-1 tab** (fig. 33: 0.500 / 0.600 / 0.200): the pad is 0.600 wide over the 0.200 nearest the thermal pad, with the extra 0.100 on its outer (+X) side. Without the tab the pattern is 180° symmetric. A rotated placement would then pass the paste-overlay check and put AVDD on SDA (review round 2, T-1).
- **Assembly marks:** F.Fab has the package outline chamfered at A1 (bottom right) and the 2D-code square of the cap at C7 (top left; DS p.35: the code marks C7, not pin 1). The silk dot sits next to A1, below the projected exclusion cones, at (+5.2, +1.6).

**Pin map:** DS p.6 fig. 4 (bottom view), mirrored. In the top view A1 is bottom-right, C1 top-right, B1 right and B7 left. AN5897 p.4 fig. 2 shows the same.

**Thermal pad (AN5897 p.3–4, section 3 and fig. 3; changed in review round 2, T-2):**
- AN5897 gives a thermal budget of 35 °C/W board-to-ambient for 320 mW at 85 °C.
- AN5897 shows 8 vias in B4, one full paste rectangle and the pad repeated on the bottom with the mask open. The review found two problems with that here:
  - Paste wicks through open vias onto the back.
  - The back pad would leave a solder bump against the bracket face and tilt the sensor.
- **Now:**
  - **4 vias** (0.3 mm drill, 0.5 mm copper) sit in one row on the centre line at x = ±0.3 and ±0.9.
  - The vias are tented on the back: no bottom pad and no bottom mask opening. They stay open on the front, inside the pad.
  - The front paste is split into **4 windows of 1.108 × 0.32 mm**, clear of the via copper by ≥ 0.03 mm. That is **51 %** of the pad.
- **Why 4, not 8:** 8 vias at JLC's 2-layer minimum (0.3 / 0.5 mm) cover the whole 2.316 × 1.200 pad and leave no room for paste windows. Keeping 8 would need smaller vias or filled and capped vias, which JLC offers for 4+ layers.
- Both layers are GND pours. 9 stitching vias tie the front pour islands to the back.
- The thermal margin on the bracket is a bench check (review T-6, V13).

**Optics (DS p.31 fig. 26, p.33 fig. 29):**
- The Rx (SPAD) "optical centre" is 1.48 mm from the left package edge and 0.10 mm below the centre line, towards the A row. The VCSEL is 4.00 mm to its right.
- The Rx centre is placed at **(0, +4.0)**, as specified, so the package centre is at (+1.72, +4.10).
- F.Fab draws the apertures. Cmts.User draws the exclusion-cone sections at 3 mm (4.2 × 4.2 square, 57.6°).

**Keep-outs:**
- The cones start at the module top, 1.75 mm above the board.
- The tallest front part is the LP5907 SOT-23-5 at 1.45 mm, and every front part is below the module top (`check_netlist.py`). So nothing on the board can enter the cones.
- There is no silk on or around the module apart from the A1 dot, which is outside its courtyard and outside the cone projection.
- The module top must stay free of tape and conformal coat. If the reel has the liner option, remove the liner after assembly (DS p.32, p.36).

### 4. Mechanics and layout

**Board:**
- 22.0 × 18.0 × 1.6 mm, R1 corners, 2 layers, ENIG.
- Two M2 holes (2.2 mm NPTH) at (±8.5, +4.0). No part is within 2.8 mm of a hole centre, which clears an M2 head of d 3.8 mm.

**Front face:** the sensor, the LDO, the LSF0204 and the passives, all lower than the sensor.

**Back face:**
- Only J1, a JST GH-6 vertical, centred at (0, −4.0). The bracket window must clear its body: about 11.3 × 6 mm footprint, 4.25 mm tall.
- Nothing else protrudes: the 4 thermal vias are tented and there is no exposed pad.
- Silk: "RABBIT ToF L8CX", the pin names "1 GND … 6 LPn" over each contact, a triangle at pin 1, "CABLE 1:1", and "rev A github.com/seralexeev/rabbit".
- Seen from the back, pin 1 is on the right (front-view X −3.125).

**Port pinout (same as the body board):**

| Pin | Net |
|---|---|
| 1 | GND |
| 2 | +3V3 (AVDD) |
| 3 | SDA |
| 4 | SCL |
| 5 | INT |
| 6 | LPn |

The mounting tabs (MP) are GND.

**Cable (review round 2, T-7):** use a JST GH 1.25 mm 6-pin double-ended cable, **same direction (pin 1 to pin 1)**, 100 mm, 26 AWG. A reverse-direction GH cable, which is just as common, puts GND on LPn and 3.3 V on INT. The back silk says "CABLE 1:1".

**Routing:**
- The power feeds are hand-routed (`design.ROUTES`), all at 0.3 mm:
  - +3V3 from J1 up the back to C1/AVDD, with a branch to the LDO input;
  - +1V8 from the LDO to C2/CORE, with a branch to the SDA/SCL pull-ups R3/R2.
- Freerouting routes the rest at 0.15 mm, plus 0.3 mm on power and GND.
- The LSF0204 is rotated 270° so that its A pins 2–5 (INT, LPn, SDA, SCL) face sensor pins A1, A2, A4 and A5 in the same order.

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
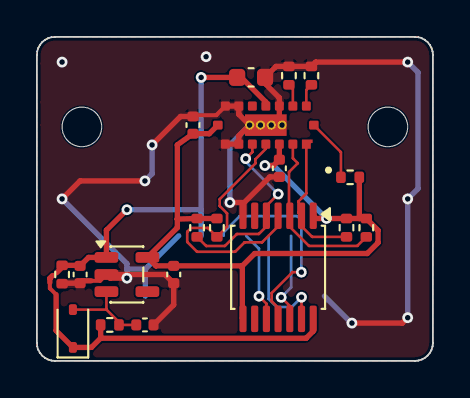
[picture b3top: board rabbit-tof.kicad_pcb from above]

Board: 2 copper layers, 22.0 x 18.0 mm, 22 parts (1 on the bottom side), 15 nets.

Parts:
C1: 10uF; C_0603_1608Metric
C2, C3: 100nF; C_0402_1005Metric
C4, C5, C6: 1uF; C_0402_1005Metric
D1: BAT54WS; D_SOD-323
H1, H2: M2; MountingHole_2.2mm_M2
J1: GH-6; JST_GH_BM06B-GHS-TBT_1x06-1MP_P1.25mm_Vertical
R1: 100k; R_0402_1005Metric
R2, R3: 2.2k; R_0402_1005Metric
R4, R5, R6, R7, R8: 47k; R_0402_1005Metric
R9: 10k; R_0402_1005Metric
U1: VL53L8CX; ST_VL53L8CX_LGA-16_6.4x3.0mm
U2: LP5907-1.8; SOT-23-5
U3: LSF0204; TSSOP-14_4.4x5mm_P0.65mm

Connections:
+1V8: C2.1, C3.2, C5.2, R2.2, R3.2, R4.2, R5.2, R6.2, U1.A3, U1.B7, U2.5, U3.1, U3.8
+3V3: C1.1, C4.2, D1.1, J1.2, R1.1, R9.1, U1.C4, U2.1, U3.14
GND: C1.2, C2.2, C3.1, C4.1, C5.1, C6.2, J1.1, J1.MP, R7.2, R8.2, R9.2, U1.A6, U1.A7, U1.B4, U1.C3, U1.C6, U1.C7, U2.2, U3.7
INT: J1.5, U3.13
INT_1V8: R4.1, U1.A1, U3.2
LDO_EN: C6.1, D1.2, R1.2, U2.3
LPN: J1.6, U3.12
LPN_1V8: R5.1, U1.A2, U3.3
NCS: R8.1, U1.C2
SCL: J1.4, U3.10
SCL_1V8: R3.1, U1.A5, U3.5
SDA: J1.3, U3.11
SDA_1V8: R2.1, U1.A4, U3.4
SPI_I2C_N: R7.1, U1.C1
SYNC_1V8: R6.1, U1.B1

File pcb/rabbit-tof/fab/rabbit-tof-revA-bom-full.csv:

Qty,Designator,Value,Footprint,LCSC,MPN / description,Side,JLC stock 2026-10-11,JLC library,Unit price USD
1,C1,10uF,C_0603_1608Metric,C19702,Samsung CL10A106KP8NNNC 10uF 10V X5R 0603,Top,10411929,base,0.0305
2,"C2,C3",100nF,C_0402_1005Metric,C1525,SMD:C 100nF X5R/X7R,Top,24111621,base,0.0045
3,"C4,C5,C6",1uF,C_0402_1005Metric,C52923,SMD:C 1uF X5R/X7R,Top,7486378,base,0.0087
1,D1,BAT54WS,D_SOD-323,C124205,Diodes BAT54WS-7-F Schottky 30 V SOD-323 (pad 1 cathode),Top,48759,expand,0.0628
1,J1,GH-6,JST_GH_BM06B-GHS-TBT_1x06-1MP_P1.25mm_Vertical,C3011957,"HCTL HC-GH-6PLT (GH-compatible, JST BM06B land; JLC stock)",Bottom,4820,expand,0.1491
1,R1,100k,R_0402_1005Metric,C25741,0402 100k 1%,Top,8084261,base,0.0024
2,"R2,R3",2.2k,R_0402_1005Metric,C25879,0402 2.2k 1%,Top,1606501,base,0.0017
5,"R4,R5,R6,R7,R8",47k,R_0402_1005Metric,C25792,0402 47k 1%,Top,5262672,base,0.0026
1,R9,10k,R_0402_1005Metric,C25744,0402 10k 1%,Top,19777407,base,0.0034
1,U1,VL53L8CX,ST_VL53L8CX_LGA-16_6.4x3.0mm,C7386355,ST VL53L8CXV0GC/1,Top,2357,expand,10.1859
1,U2,LP5907-1.8,SOT-23-5,C92498,TI LP5907MFX-1.8/NOPB,Top,30782,expand,0.1922
1,U3,LSF0204,TSSOP-14_4.4x5mm_P0.65mm,C202288,TI LSF0204PWR,Top,10106,expand,0.6336

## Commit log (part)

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2025-05-13 docs: add vpn + ssh
2025-05-25 add python
2025-05-25 mechanics
2025-07-02 fix docker webrtc
2025-07-04 nats
2025-07-04 drop ros2
2025-07-06 monitoring
2025-07-21 fix rpc and deps
2025-07-23 add optimized models
2025-07-23 move zed
2025-08-18 Track large binaries with Git LFS
2026-02-01 Add images to README
2026-02-01 Update project title with link in README
